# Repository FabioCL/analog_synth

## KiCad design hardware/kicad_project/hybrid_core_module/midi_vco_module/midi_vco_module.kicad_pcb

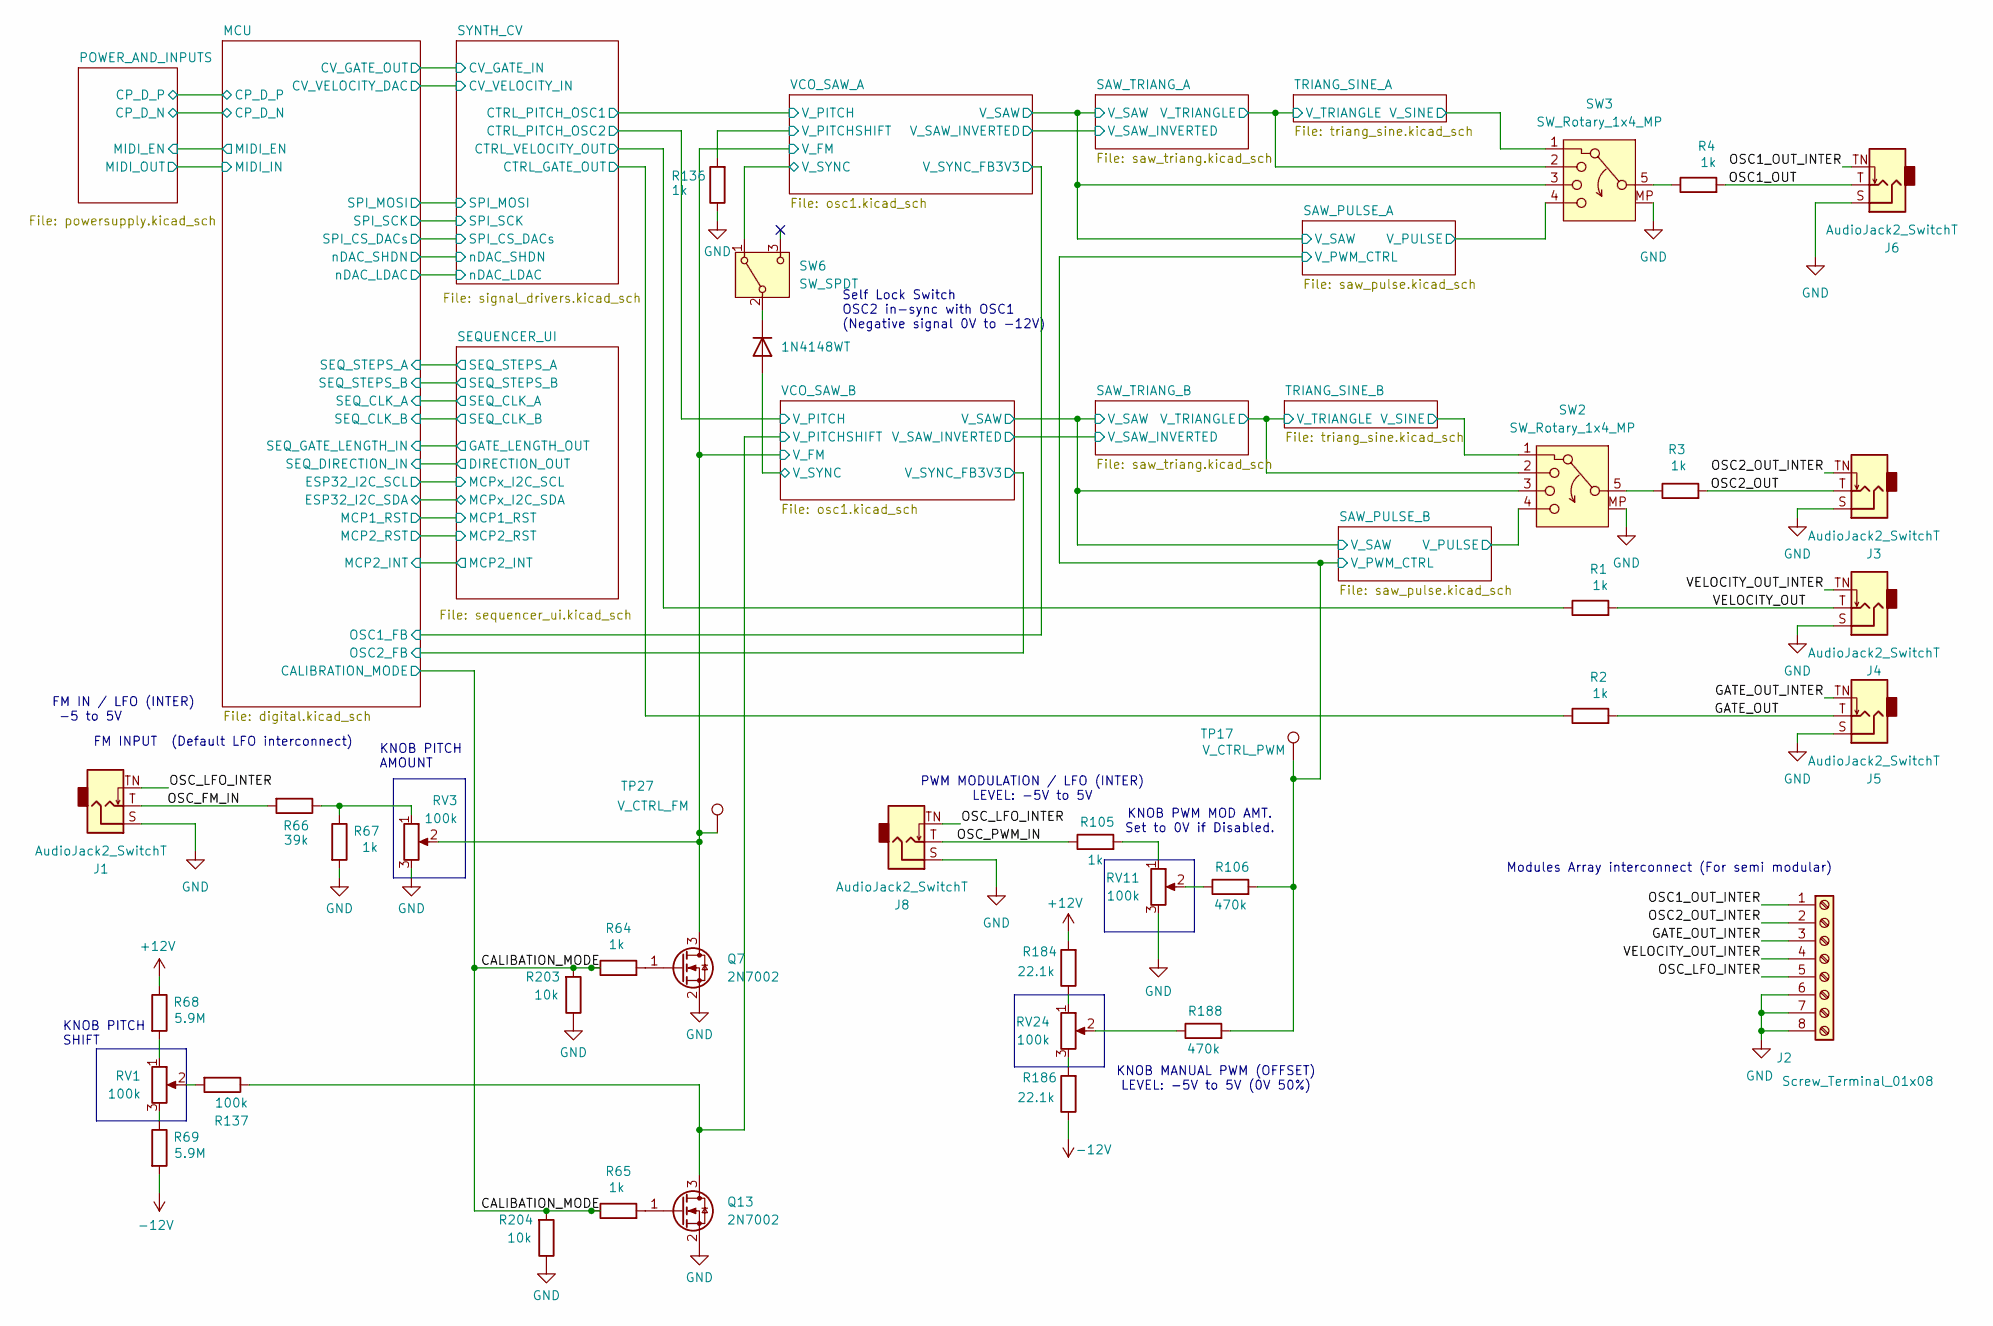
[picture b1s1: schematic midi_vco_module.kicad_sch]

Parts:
D1: 1N4148WT; D_SOD-523; Manufacturer PartNumer 1N4148WT
J1, J3, J4, J5, J6, J8: AudioJack2_SwitchT; Jack_3.5mm_QingPu_WQP-PJ398SM_Vertical_CircularHoles; Manufacturer PartNumer WQP-PJ398SM
J2: Screw_Terminal_01x08; TerminalBlock_CUI_TB007-508-08_1x08_P5.08mm_Horizontal; Manufacturer PartNumer TB007-508-08BE
Q7, Q13: 2N7002; SOT-23; Manufacturer PartNumer 2N7002
R1, R2, R3, R4, R64, R65, R67, R105, R136: 1k; R_0402_1005Metric; Manufacturer PartNumer RT0402FRE071KL
R66: 39k; R_0402_1005Metric; Manufacturer PartNumer RT0402FRE0739KL
R68, R69: 5.9M; R_0402_1005Metric; Manufacturer PartNumer RC0402FR-075M9L
R106, R188: 470k; R_0402_1005Metric; Manufacturer PartNumer RC0402FR-7D470KL
R137: 100k; R_0402_1005Metric; Manufacturer PartNumer RT0402FRE07100KL
R184, R186: 22.1k; R_0402_1005Metric; Manufacturer PartNumer RT0402FRE0721KL
R203, R204: 10k; R_0402_1005Metric; Manufacturer PartNumer RT0402FRE0710KL
RV1, RV3, RV11, RV24: 100k; Potentiometer_RV09_Single_Vertical; Manufacturer PartNumer 3296W-104-LF
SW2, SW3: SW_Rotary_1x4_MP; SR16 Rotary Band Switch; Manufacturer PartNumer SR16
SW6: SW_SPDT; SW_Toggle_Blue_wSlots; Manufacturer PartNumer MTS-102
TP17: V_CTRL_PWM; TestPoint_Pad_1.0x1.0mm
TP27: V_CTRL_FM; TestPoint_Pad_1.0x1.0mm

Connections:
+12V: R68.1, R184.2; also elsewhere on the board
-12V: R69.2, R186.1; also elsewhere on the board
/CALIBATION_MODE: R64.1, R65.1, R203.2, R204.2; also elsewhere on the board
/GATE_OUT: J5.T, R2.2
/GATE_OUT_INTER: J2.3, J5.TN
/OSC1_OUT: J6.T, R4.2
/OSC1_OUT_INTER: J2.1, J6.TN
/OSC2_OUT: J3.T, R3.2
/OSC2_OUT_INTER: J2.2, J3.TN
/OSC_FM_IN: J1.T, R66.2
/OSC_LFO_INTER: J1.TN, J2.5, J8.TN
/OSC_PWM_IN: J8.T, R105.1
/SAW_PULSE_A/V_PULSE: SW3.4; also elsewhere on the board
/SAW_PULSE_A/V_PWM_CTRL: R106.2, R188.2, TP17.1; also elsewhere on the board
/SAW_PULSE_A/V_SAW: SW3.3; also elsewhere on the board
/SAW_PULSE_B/V_PULSE: SW2.4; also elsewhere on the board
/SAW_PULSE_B/V_SAW: SW2.3; also elsewhere on the board
/SAW_TRIANG_A/V_TRIANGLE: SW3.2; also elsewhere on the board
/SAW_TRIANG_B/V_TRIANGLE: SW2.2; also elsewhere on the board
/SYNTH_CV/CTRL_GATE_OUT: R2.1; also elsewhere on the board
/SYNTH_CV/CTRL_VELOCITY_OUT: R1.1; also elsewhere on the board
/TRIANG_SINE_A/V_SINE: SW3.1; also elsewhere on the board
/TRIANG_SINE_B/V_SINE: SW2.1; also elsewhere on the board
/VCO_SAW_A/V_FM: Q7.3 (D), RV3.2, TP27.1; also elsewhere on the board
/VCO_SAW_A/V_PITCHSHIFT: R136.2; also elsewhere on the board
/VCO_SAW_A/V_SYNC: SW6.1 (A); also elsewhere on the board
/VCO_SAW_B/V_PITCHSHIFT: Q13.3 (D), R137.1; also elsewhere on the board
/VCO_SAW_B/V_SYNC: D1.2 (A); also elsewhere on the board
/VELOCITY_OUT: J4.T, R1.2
/VELOCITY_OUT_INTER: J2.4, J4.TN
GND: J1.S, J2.6, J2.7, J2.8, J3.S, J4.S, J5.S, J6.S, J8.S, Q7.2 (S), Q13.2 (S), R67.2, R136.1, R203.1, R204.1, RV3.3, RV11.3, SW2.MP, SW3.MP; also elsewhere on the board
unnamed: D1.1 (K), SW6.2 (B)
unnamed: Q7.1 (G), R64.2
unnamed: Q13.1 (G), R65.2
unnamed: R3.1, SW2.5
unnamed: R4.1, SW3.5
unnamed: R66.1, R67.1, RV3.1
unnamed: R68.2, RV1.1
unnamed: R69.1, RV1.3
unnamed: R105.2, RV11.1
unnamed: R106.1, RV11.2
unnamed: R137.2, RV1.2
unnamed: R184.1, RV24.1
unnamed: R186.2, RV24.3
unnamed: R188.1, RV24.2

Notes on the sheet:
KNOB PITCH SHIFT
KNOB PWM MOD AMT. Set to 0V if Disabled.
Self Lock Switch OSC2 in-sync with OSC1 (Negative signal 0V to -12V)
PWM MODULATION / LFO (INTER) LEVEL: -5V to 5V
FM INPUT (Default LFO interconnect)
KNOB MANUAL PWM (OFFSET) LEVEL: -5V to 5V (0V 50%)
KNOB PITCH AMOUNT
FM IN / LFO (INTER) -5 to 5V
Modules Array interconnect (For semi modular)

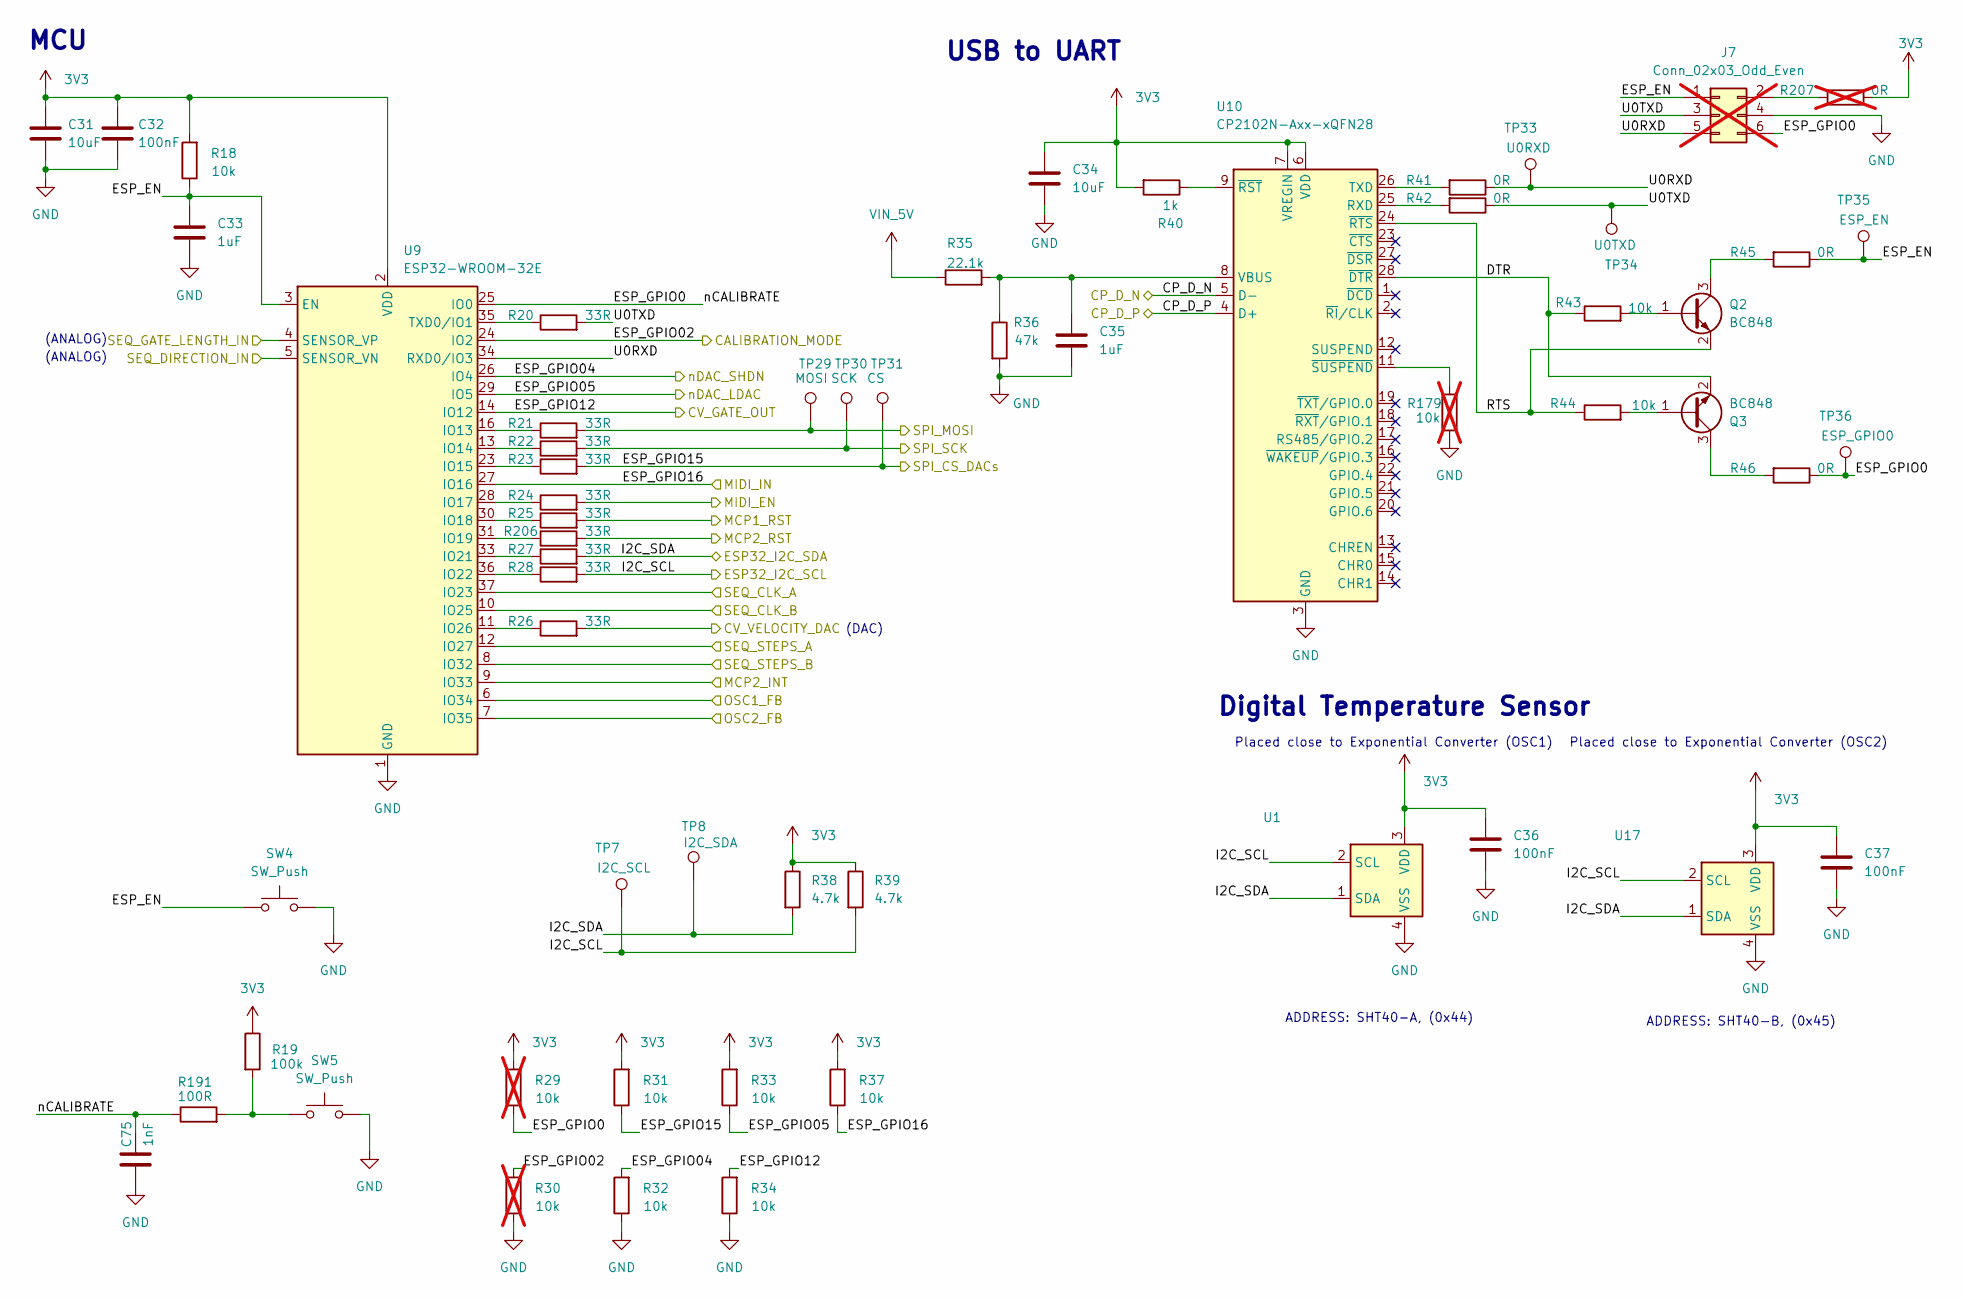
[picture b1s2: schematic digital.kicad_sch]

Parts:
C31, C34: 10uF; C_0805_2012Metric; Manufacturer PartNumer GRM21BR61E106KA73K
C32, C36, C37: 100nF; C_0402_1005Metric; Manufacturer PartNumer GRM155R71E104KE14J
C33, C35: 1uF; C_0805_2012Metric; Manufacturer PartNumer GRM219R71E105MA88J
C75: 1nF; C_0402_1005Metric; Manufacturer PartNumer GRM155R71E103KA01J
J7: Conn_02x03_Odd_Even; PinHeader_2x03_P1.27mm_Vertical_SMD; not fitted
Q2, Q3: BC848; SOT-23; Manufacturer PartNumer BC848A
R18, R31, R32, R33, R34, R37, R43, R44: 10k; R_0402_1005Metric; Manufacturer PartNumer RT0402FRE0710KL
R19: 100k; R_0402_1005Metric; Manufacturer PartNumer RT0402FRE07100KL
R20, R21, R22, R23, R24, R25, R26, R27, R28, R206: 33R; R_0402_1005Metric; Manufacturer PartNumer RT0402FRE0733RL
R29, R30, R179: 10k; R_0402_1005Metric; Manufacturer PartNumer RT0402FRE0710KL; not fitted
R35: 22.1k; R_0402_1005Metric; Manufacturer PartNumer RT0402FRE0721KL
R36: 47k; R_0402_1005Metric; Manufacturer PartNumer RT0402FRE0747KL
R38, R39: 4.7k; R_0402_1005Metric; Manufacturer PartNumer RT0402FRE074K7L
R40: 1k; R_0402_1005Metric; Manufacturer PartNumer RT0402FRE071KL
R41, R42, R45, R46: 0R; R_0402_1005Metric; Manufacturer PartNumer RC0402FR-070RL
R191: 100R; R_0402_1005Metric; Manufacturer PartNumer RT0402FRE07100RL
R207: 0R; R_0402_1005Metric; Manufacturer PartNumer RC0402FR-070RL; not fitted
SW4, SW5: SW_Push; SW_PUSH_6mm
TP7: I2C_SCL; TestPoint_Pad_1.0x1.0mm
TP8: I2C_SDA; TestPoint_Pad_1.0x1.0mm
TP29: MOSI; TestPoint_Pad_1.0x1.0mm
TP30: SCK; TestPoint_Pad_1.0x1.0mm
TP31: CS; TestPoint_Pad_1.0x1.0mm
TP33: U0RXD; TestPoint_Pad_1.0x1.0mm
TP34: U0TXD; TestPoint_Pad_1.0x1.0mm
TP35: ESP_EN; TestPoint_Pad_1.0x1.0mm
TP36: ESP_GPIO0; TestPoint_Pad_1.0x1.0mm
U1: SHT4x; Sensirion_DFN-4_1.5x1.5mm_P0.8mm_SHT4x_NoCentralPad; Manufacturer PartNumer SHT40-AD1B-R3
U9: ESP32-WROOM-32E; ESP32-WROOM-32D; Manufacturer PartNumer ESP32-WROOM-32E-N8
U10: CP2102N-Axx-xQFN28; QFN-28-1EP_5x5mm_P0.5mm_EP3.35x3.35mm; Manufacturer PartNumer CP2102N-A02-GQFN28R
U17: SHT4x; Sensirion_DFN-4_1.5x1.5mm_P0.8mm_SHT4x_NoCentralPad; Manufacturer PartNumer SHT40-BD1B-R3

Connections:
3V3: C31.1, C32.1, C34.1, C36.1, C37.1, R18.2, R19.1, R29.2, R31.2, R33.2, R37.2, R38.1, R39.1, R40.2, R207.1, U1.3 (VDD), U9.2 (VDD), U10.6 (VDD), U10.7 (VREGIN), U17.3 (VDD); also elsewhere on the board
/CALIBATION_MODE: R30.2, U9.24 (IO2); also elsewhere on the board
/MCU/CP_D_N: U10.5 (D-); also elsewhere on the board
/MCU/CP_D_P: U10.4 (D+); also elsewhere on the board
/MCU/CV_VELOCITY_DAC: R26.2; also elsewhere on the board
/MCU/DTR: Q3.2 (E), R43.1, U10.28 (~DTR)
/MCU/ESP_EN: C33.1, J7.1, R18.1, R45.1, SW4.1, TP35.1, U9.3 (EN)
/MCU/ESP_GPIO0: C75.2, J7.6, R29.1, R46.1, R191.1, TP36.1, U9.25 (IO0)
/MCU/ESP_GPIO04: R32.2, U9.26 (IO4); also elsewhere on the board
/MCU/ESP_GPIO05: R33.1, U9.29 (IO5); also elsewhere on the board
/MCU/ESP_GPIO12: R34.2, U9.14 (IO12); also elsewhere on the board
/MCU/ESP_GPIO15: R23.2, R31.1, TP31.1; also elsewhere on the board
/MCU/ESP_GPIO16: R37.1, U9.27 (IO16); also elsewhere on the board
/MCU/I2C_SCL: R28.2, R39.2, TP7.1, U1.2 (SCL), U17.2 (SCL); also elsewhere on the board
/MCU/I2C_SDA: R27.2, R38.2, TP8.1, U1.1 (SDA), U17.1 (SDA); also elsewhere on the board
/MCU/MCP2_INT: U9.9 (IO33); also elsewhere on the board
/MCU/MCP2_RST: R206.2; also elsewhere on the board
/MCU/MIDI_EN: R24.2; also elsewhere on the board
/MCU/OSC1_FB: U9.6 (IO34); also elsewhere on the board
/MCU/OSC2_FB: U9.7 (IO35); also elsewhere on the board
/MCU/RTS: Q2.2 (E), R44.1, U10.24 (~RTS)
/MCU/SEQ_CLK_A: U9.37 (IO23); also elsewhere on the board
/MCU/SEQ_CLK_B: U9.10 (IO25); also elsewhere on the board
/MCU/SEQ_DIRECTION_IN: U9.5 (SENSOR_VN); also elsewhere on the board
/MCU/SEQ_GATE_LENGTH_IN: U9.4 (SENSOR_VP); also elsewhere on the board
/MCU/SEQ_STEPS_A: U9.12 (IO27); also elsewhere on the board
/MCU/SEQ_STEPS_B: U9.8 (IO32); also elsewhere on the board
/MCU/U0RXD: J7.5, R41.1, TP33.1, U9.34 (RXD0/IO3)
/MCU/U0TXD: J7.3, R20.2, R42.1, TP34.1
/SEQUENCER_UI/MCP_RST: R25.2; also elsewhere on the board
/SYNTH_CV/SPI_MOSI: R21.2, TP29.1; also elsewhere on the board
/SYNTH_CV/SPI_SCK: R22.2, TP30.1; also elsewhere on the board
GND: C31.2, C32.2, C33.2, C34.2, C35.2, C36.2, C37.2, C75.1, J7.4, R30.1, R32.1, R34.1, R36.2, R179.1, SW4.2, SW5.2, U1.4 (VSS), U9.1 (GND), U9.15 (GND), U9.38 (GND), U9.39 (GND), U10.3 (GND), U10.29 (GND), U17.4 (VSS); also elsewhere on the board
unnamed: J7.2, R207.2
unnamed: Q2.1 (B), R43.2
unnamed: Q2.3 (C), R45.2
unnamed: Q3.1 (B), R44.2
unnamed: Q3.3 (C), R46.2
unnamed: R19.2, R191.2, SW5.1
unnamed: R21.1, U9.16 (IO13)
unnamed: R22.1, U9.13 (IO14)
unnamed: R23.1, U9.23 (IO15)
unnamed: R24.1, U9.28 (IO17)
unnamed: R25.1, U9.30 (IO18)
unnamed: R206.1, U9.31 (IO19)
unnamed: R27.1, U9.33 (IO21)
unnamed: R28.1, U9.36 (IO22)
unnamed: R26.1, U9.11 (IO26)
unnamed: R20.1, U9.35 (TXD0/IO1)
unnamed: R42.2, U10.25 (RXD)
unnamed: R41.2, U10.26 (TXD)
unnamed: C35.1, R35.2, R36.1, U10.8 (VBUS)
unnamed: R40.1, U10.9 (~RST)
unnamed: R179.2, U10.11 (~SUSPEND)
VIN_5V: R35.1; also elsewhere on the board

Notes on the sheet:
ADDRESS: SHT40-A, (0x44)
USB to UART
Placed close to Exponential Converter (OSC1)
Placed close to Exponential Converter (OSC2)
(ANALOG)
(DAC)
ADDRESS: SHT40-B, (0x45)
Digital Temperature Sensor
MCU

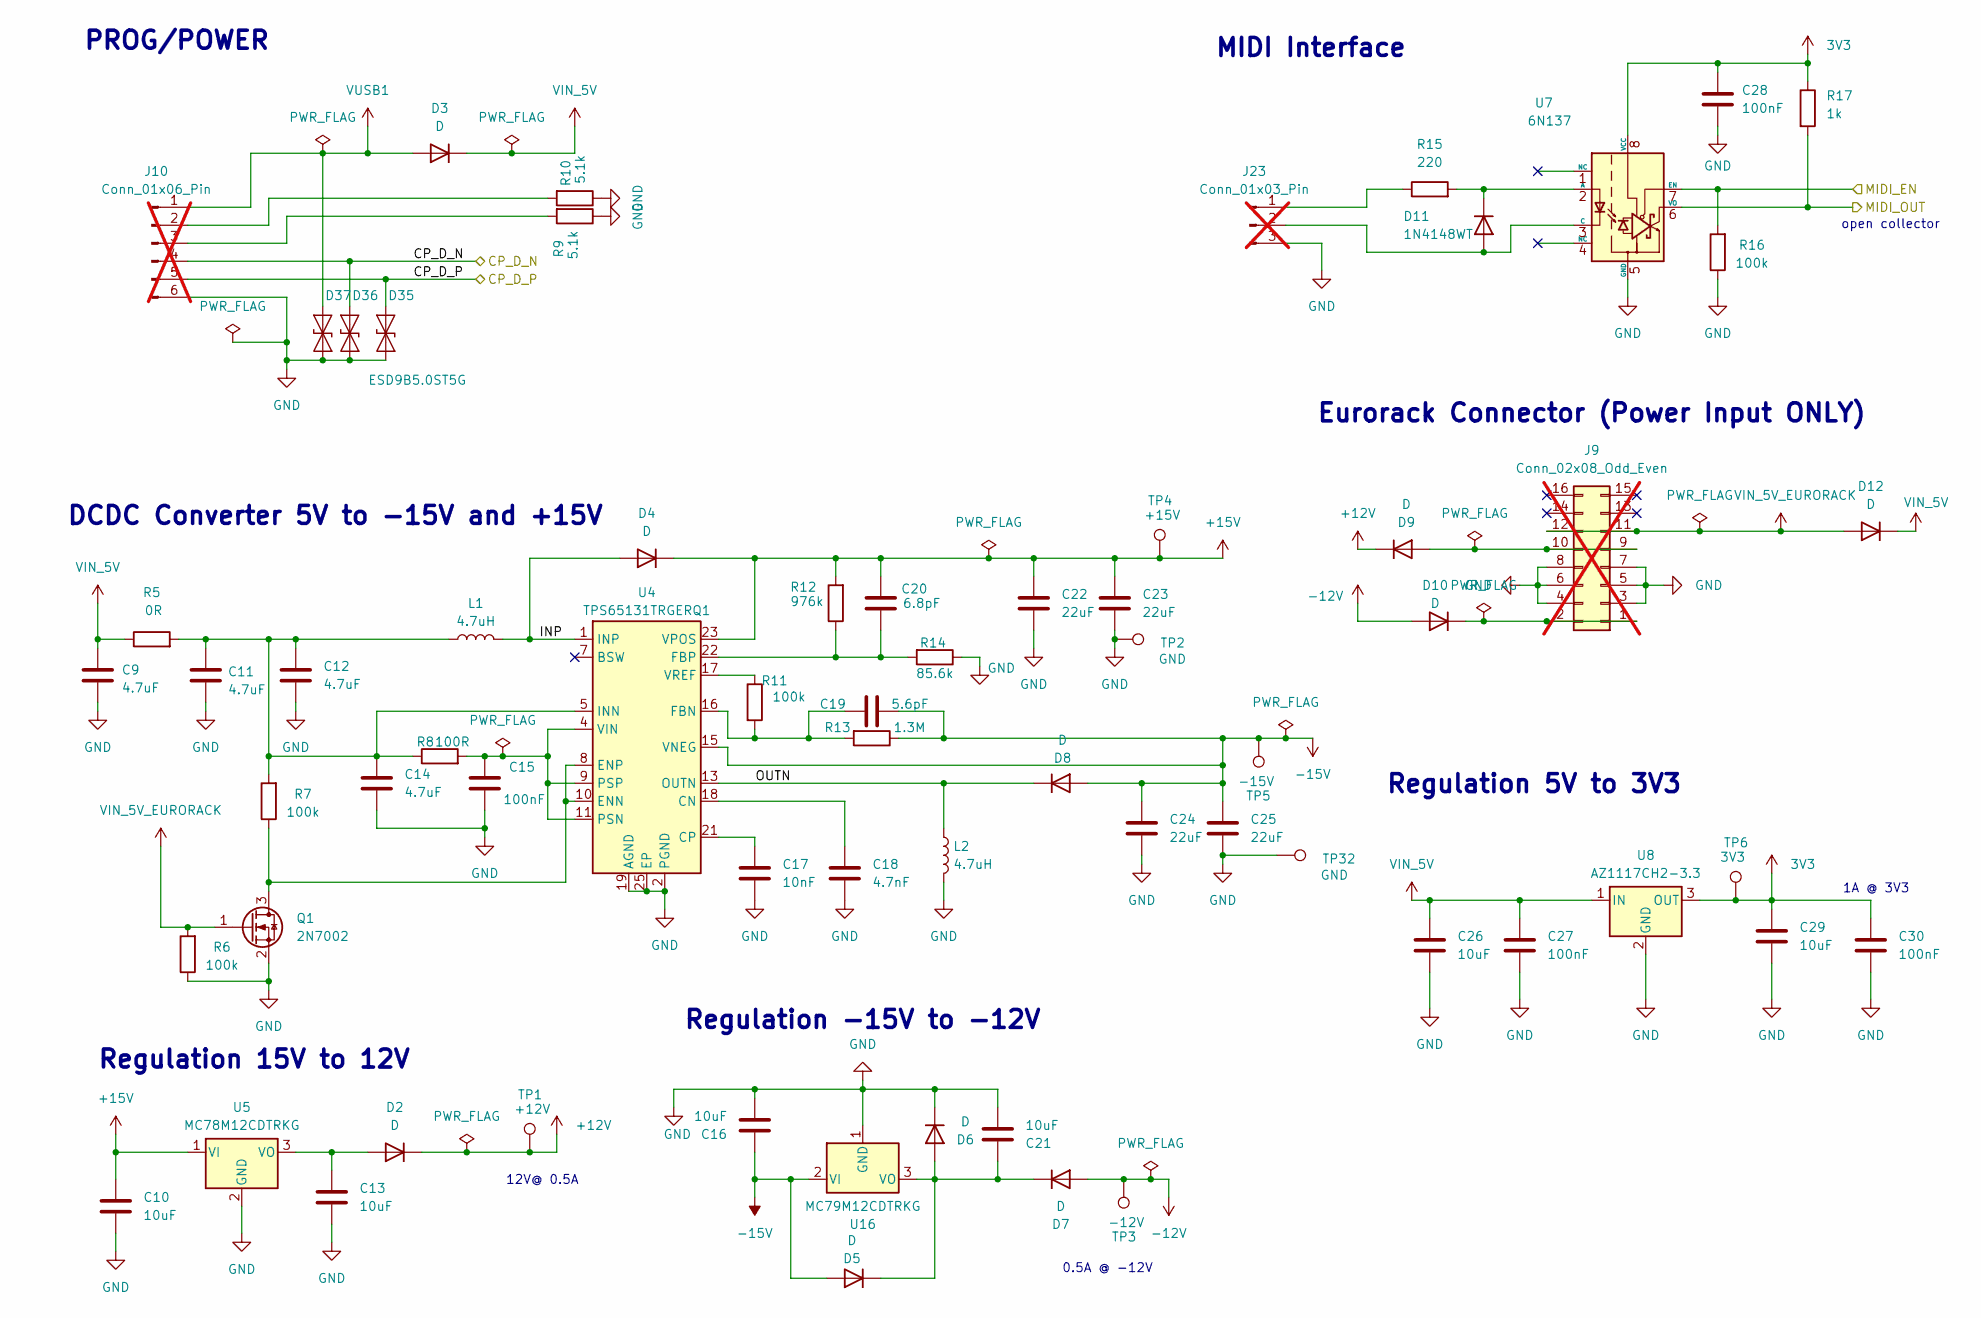
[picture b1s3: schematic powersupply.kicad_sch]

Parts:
C9, C11, C12, C14: 4.7uF; C_0805_2012Metric; Manufacturer PartNumer GRM219R61E475MA73D
C10, C13, C16, C21, C26, C29: 10uF; C_0805_2012Metric; Manufacturer PartNumer GRM21BR61E106KA73K
C15, C27, C28, C30: 100nF; C_0402_1005Metric; Manufacturer PartNumer GRM155R71E104KE14J
C17: 10nF; C_0402_1005Metric; Manufacturer PartNumer GRM155R71E103KA01D
C18: 4.7nF; C_0402_1005Metric; Manufacturer PartNumer GRM155R71E472KA01J
C19: 5.6pF; C_0402_1005Metric; Manufacturer PartNumer GJM1555C1H5R6BB01J
C20: 6.8pF; C_0402_1005Metric; Manufacturer PartNumer GJM1555C1H6R8DB01D
C22, C23, C24, C25: 22uF; C_1210_3225Metric; Manufacturer PartNumer CL32A226KAJNNNE
D2, D3, D4, D5, D6, D7, D8, D9, D10, D12: D; D_Powermite_AK; Manufacturer PartNumer MBRM120LT1G
D11: 1N4148WT; D_SOD-523; Manufacturer PartNumer 1N4148WT
D35, D36, D37: ESD9B5.0ST5G; D_SOD-923; Manufacturer PartNumer ESD9B5.0ST5G
J9: Conn_02x08_Odd_Even; PinHeader_2x08_P2.54mm_Vertical; Manufacturer PartNumer TST-108-02-T-D; not fitted
J10: Conn_01x06_Pin; PinHeader_1x06_P2.54mm_Vertical; not fitted
J23: Conn_01x03_Pin; PinHeader_1x03_P2.54mm_Vertical; not fitted
L1, L2: 4.7uH; L_TDK_SLF6028; Manufacturer PartNumer SLF6028T-4R7M1R6-PF
Q1: 2N7002; SOT-23; Manufacturer PartNumer 2N7002
R5: 0R; R_1210_3225Metric; Manufacturer PartNumer RC0402FR-070RL
R6, R7, R11, R16: 100k; R_0402_1005Metric; Manufacturer PartNumer RT0402FRE07100KL
R8: 100R; R_0402_1005Metric; Manufacturer PartNumer RT0402FRE07100RL
R9, R10: 5.1k; R_0402_1005Metric; Manufacturer PartNumer RT0402FRE075K1L
R12: 976k; R_0402_1005Metric; Manufacturer PartNumer RC0402FR-07976KL
R13: 1.3M; R_0402_1005Metric; Manufacturer PartNumer RC0402FR-071M3L
R14: 85.6k; R_0402_1005Metric; Manufacturer PartNumer RT0402BRE0785K6L
R15: 220; R_0402_1005Metric; Manufacturer PartNumer RT0402FRE07220RL
R17: 1k; R_0402_1005Metric; Manufacturer PartNumer RT0402FRE071KL
TP1: +12V; TestPoint_Pad_1.0x1.0mm
TP2, TP32: GND; TestPoint_Pad_1.0x1.0mm
TP3: -12V; TestPoint_Pad_1.0x1.0mm
TP4: +15V; TestPoint_Pad_1.0x1.0mm
TP5: -15V; TestPoint_Pad_1.0x1.0mm
TP6: 3V3; TestPoint_Pad_1.0x1.0mm
U4: TPS65131TRGERQ1; VQFN-24-1EP_4x4mm_P0.5mm_EP2.45x2.45mm_ThermalVias; Manufacturer PartNumer TPS65131TRGERQ1
U5: MC78M12CDTRKG; TO-252-2; Manufacturer PartNumer MC78M12CDTRKG
U7: 6N137; DIP-8_W7.62mm; Manufacturer PartNumer 6N137-X007T
U8: AZ1117CH2-3.3; SOT-223-3_TabPin2; Manufacturer PartNumer AZ1117CH2-3.3TRG1
U16: MC79M12CDTRKG; TO-252-2; Manufacturer PartNumer MC79M12CDTRKG

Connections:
3V3: C28.1, C29.1, C30.1, R17.1, TP6.1, U7.8 (VCC), U8.3 (OUT); also elsewhere on the board
+12V: D2.1 (K), D9.1 (K), TP1.1; also elsewhere on the board
+15V: C10.1, C20.1, C22.1, C23.1, D4.1 (K), R12.2, TP4.1, U4.23 (VPOS), U5.1 (VI)
-12V: D7.2 (A), D10.2 (A), TP3.1; also elsewhere on the board
-15V: C16.1, C19.2, C24.1, C25.1, D5.2 (A), D8.2 (A), R13.1, TP5.1, U4.15 (VNEG), U16.2 (VI)
/MCU/CP_D_N: D36.2 (A2), J10.4; also elsewhere on the board
/MCU/CP_D_P: D35.2 (A2), J10.5; also elsewhere on the board
/MCU/ESP_GPIO16: R17.2, U7.6 (VO); also elsewhere on the board
/MCU/MIDI_EN: R16.2, U7.7 (EN); also elsewhere on the board
/POWER_AND_INPUTS/INP: D4.2 (A), L1.2, U4.1 (INP), U4.24 (INP)
/POWER_AND_INPUTS/OUTN: D8.1 (K), L2.1, U4.13 (OUTN), U4.14 (OUTN)
GND: C9.2, C10.2, C11.2, C12.2, C13.2, C14.2, C15.2, C16.2, C17.2, C18.2, C21.2, C22.2, C23.2, C24.2, C25.2, C26.2, C27.2, C28.2, C29.2, C30.2, D6.1 (K), D35.1 (A1), D36.1 (A1), D37.1 (A1), J9.3, J9.4, J9.5, J9.6, J9.7, J9.8, J10.6, J23.3, L2.2, Q1.2 (S), R6.1, R9.1, R10.1, R14.1, R16.1, TP2.1, TP32.1, U4.2 (PGND), U4.3 (PGND), U4.19 (AGND), U4.25 (EP), U5.2 (GND), U7.5 (GND), U8.2 (GND), U16.1 (GND); also elsewhere on the board
unnamed: C11.1, C12.1, C14.1, L1.1, R5.2, R7.2, R8.1, U4.5 (INN), U4.6 (INN)
unnamed: C13.1, D2.2 (A), U5.3 (VO)
unnamed: C21.1, D5.1 (K), D6.2 (A), D7.1 (K), U16.3 (VO)
unnamed: D9.2 (A), J9.9, J9.10
unnamed: D10.1 (K), J9.1, J9.2
unnamed: D11.2 (A), J23.2, U7.3 (C)
unnamed: D11.1 (K), R15.2, U7.2 (A)
unnamed: J10.2, R10.2
unnamed: J10.3, R9.2
unnamed: J23.1, R15.1
unnamed: Q1.3 (D), R7.1, U4.8 (ENP), U4.10 (ENN)
unnamed: C18.1, U4.18 (CN)
unnamed: C17.1, U4.21 (CP)
unnamed: C19.1, R11.2, R13.2, U4.16 (FBN)
unnamed: C20.2, R12.1, R14.2, U4.22 (FBP)
unnamed: C15.1, R8.2, U4.4 (VIN), U4.9 (PSP), U4.11 (PSN)
unnamed: R11.1, U4.17 (VREF)
VIN_5V: C9.1, C26.1, C27.1, D3.1 (K), D12.1 (K), R5.1, U8.1 (IN); also elsewhere on the board
VIN_5V_EURORACK: D12.2 (A), J9.11, J9.12, Q1.1 (G), R6.2
VUSB1: D3.2 (A), D37.2 (A2), J10.1

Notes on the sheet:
12V@ 0.5A
DCDC Converter 5V to -15V and +15V
0.5A @ -12V
Regulation -15V to -12V
MIDI Interface
Regulation 15V to 12V
1A @ 3V3
Eurorack Connector (Power Input ONLY)
Regulation 5V to 3V3
open collector
PROG/POWER

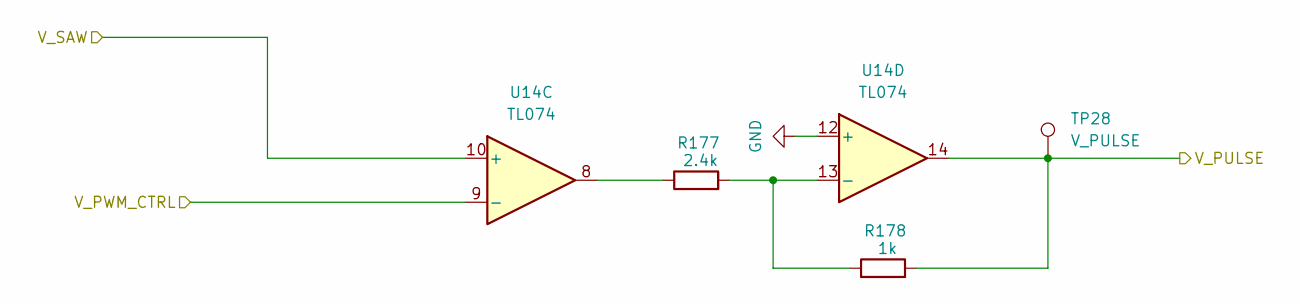
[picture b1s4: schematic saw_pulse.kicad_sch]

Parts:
R177: 2.4k; R_0402_1005Metric; Manufacturer PartNumer RT0402BRD072K4L
R178: 1k; R_0402_1005Metric; Manufacturer PartNumer RT0402FRE071KL
TP28: V_PULSE; TestPoint_Pad_1.0x1.0mm
U14: TL074; SOIC-14_3.9x8.7mm_P1.27mm; Manufacturer PartNumer TL074HIDR

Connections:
/SAW_PULSE_A/V_PULSE: R178.2, TP28.1, U14.14; also elsewhere on the board
/SAW_PULSE_A/V_PWM_CTRL: U14.9 (-); also elsewhere on the board
/SAW_PULSE_A/V_SAW: U14.10 (+); also elsewhere on the board
GND: U14.12 (+); also elsewhere on the board
unnamed: R177.1, U14.8
unnamed: R177.2, R178.1, U14.13 (-)

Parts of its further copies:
R107: 2.4k; R_0402_1005Metric; Manufacturer PartNumer RT0402BRD072K4L
R108: 1k; R_0402_1005Metric; Manufacturer PartNumer RT0402FRE071KL
TP18: V_PULSE; TestPoint_Pad_1.0x1.0mm
U24: TL074; SOIC-14_3.9x8.7mm_P1.27mm; Manufacturer PartNumer TL074HIDR

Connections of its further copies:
+12V: U24.4 (V+); also elsewhere on the board
-12V: U24.11 (V-); also elsewhere on the board
/SAW_PULSE_A/V_PWM_CTRL: U24.9 (-); also elsewhere on the board
/SAW_PULSE_B/V_PULSE: R108.2, TP18.1, U24.14; also elsewhere on the board
/SAW_PULSE_B/V_SAW: U24.10 (+); also elsewhere on the board
/SAW_TRIANG_B/V_TRIANGLE: U24.1; also elsewhere on the board
/TRIANG_SINE_B/V_SINE: U24.7; also elsewhere on the board
GND: U24.12 (+); also elsewhere on the board
unnamed 158: U24.5 (+); also elsewhere on the board
unnamed: R107.1, U24.8
unnamed 268: U24.3 (+); also elsewhere on the board
unnamed 269: U24.2 (-); also elsewhere on the board
unnamed 270: U24.6 (-); also elsewhere on the board
unnamed: R107.2, R108.1, U24.13 (-)

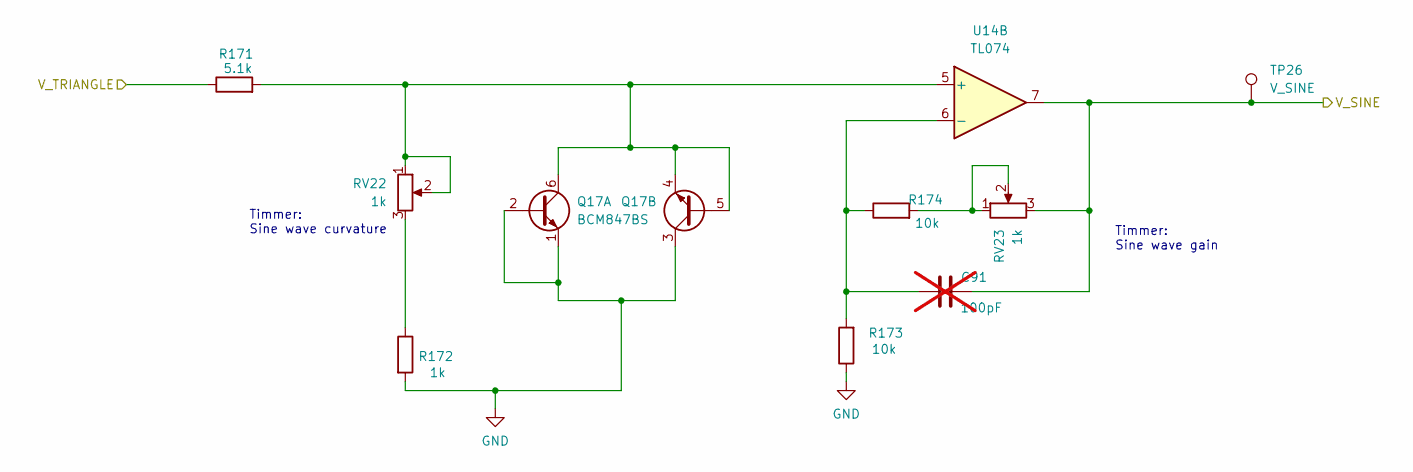
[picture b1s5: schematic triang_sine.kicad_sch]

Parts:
C91: 100pF; C_0402_1005Metric; Manufacturer PartNumer GCM1555C1H101FA16J; not fitted
Q17: BCM847BS; SOT-363_SC-70-6; Manufacturer PartNumer BCM847BS
R171: 5.1k; R_0402_1005Metric; Manufacturer PartNumer RT0402FRE075K1L
R172: 1k; R_0402_1005Metric; Manufacturer PartNumer RT0402FRE071KL
R173, R174: 10k; R_0402_1005Metric; Manufacturer PartNumer RT0402FRE0710KL
RV22, RV23: 1k; Potentiometer_Bourns_3296W_Vertical; Manufacturer PartNumer 3296W-102-LF
TP26: V_SINE; TestPoint_Pad_1.0x1.0mm
U14: TL074; SOIC-14_3.9x8.7mm_P1.27mm; Manufacturer PartNumer TL074HIDR

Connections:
/SAW_TRIANG_A/V_TRIANGLE: R171.1; also elsewhere on the board
/TRIANG_SINE_A/V_SINE: C91.2, RV23.3, TP26.1, U14.7; also elsewhere on the board
GND: Q17.1 (E1), Q17.2 (B1), Q17.3 (C2), R172.2, R173.1; also elsewhere on the board
unnamed: Q17.4 (E2), Q17.5 (B2), Q17.6 (C1), R171.2, RV22.1, RV22.2, U14.5 (+)
unnamed: R172.1, RV22.3
unnamed: R174.2, RV23.1, RV23.2
unnamed: C91.1, R173.2, R174.1, U14.6 (-)

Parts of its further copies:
C66: 100pF; C_0402_1005Metric; Manufacturer PartNumer GCM1555C1H101FA16J; not fitted
Q11: BCM847BS; SOT-363_SC-70-6; Manufacturer PartNumer BCM847BS
R101: 5.1k; R_0402_1005Metric; Manufacturer PartNumer RT0402FRE075K1L
R102: 1k; R_0402_1005Metric; Manufacturer PartNumer RT0402FRE071KL
R103, R104: 10k; R_0402_1005Metric; Manufacturer PartNumer RT0402FRE0710KL
RV9, RV10: 1k; Potentiometer_Bourns_3296W_Vertical; Manufacturer PartNumer 3296W-102-LF
TP16: V_SINE; TestPoint_Pad_1.0x1.0mm
U24: TL074; SOIC-14_3.9x8.7mm_P1.27mm; Manufacturer PartNumer TL074HIDR

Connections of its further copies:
+12V: U24.4 (V+); also elsewhere on the board
-12V: U24.11 (V-); also elsewhere on the board
/SAW_PULSE_A/V_PWM_CTRL: U24.9 (-); also elsewhere on the board
/SAW_PULSE_B/V_PULSE: U24.14; also elsewhere on the board
/SAW_PULSE_B/V_SAW: U24.10 (+); also elsewhere on the board
/SAW_TRIANG_B/V_TRIANGLE: R101.1, U24.1; also elsewhere on the board
/TRIANG_SINE_B/V_SINE: C66.2, RV10.3, TP16.1, U24.7; also elsewhere on the board
GND: Q11.1 (E1), Q11.2 (B1), Q11.3 (C2), R102.2, R103.1, U24.12 (+); also elsewhere on the board
unnamed: Q11.4 (E2), Q11.5 (B2), Q11.6 (C1), R101.2, RV9.1, RV9.2, U24.5 (+)
unnamed: R102.1, RV9.3
unnamed: R104.2, RV10.1, RV10.2
unnamed 190: U24.8; also elsewhere on the board
unnamed 268: U24.3 (+); also elsewhere on the board
unnamed 269: U24.2 (-); also elsewhere on the board
unnamed: C66.1, R103.2, R104.1, U24.6 (-)
unnamed 271: U24.13 (-); also elsewhere on the board

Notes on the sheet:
Timmer: Sine wave gain
Timmer: Sine wave curvature

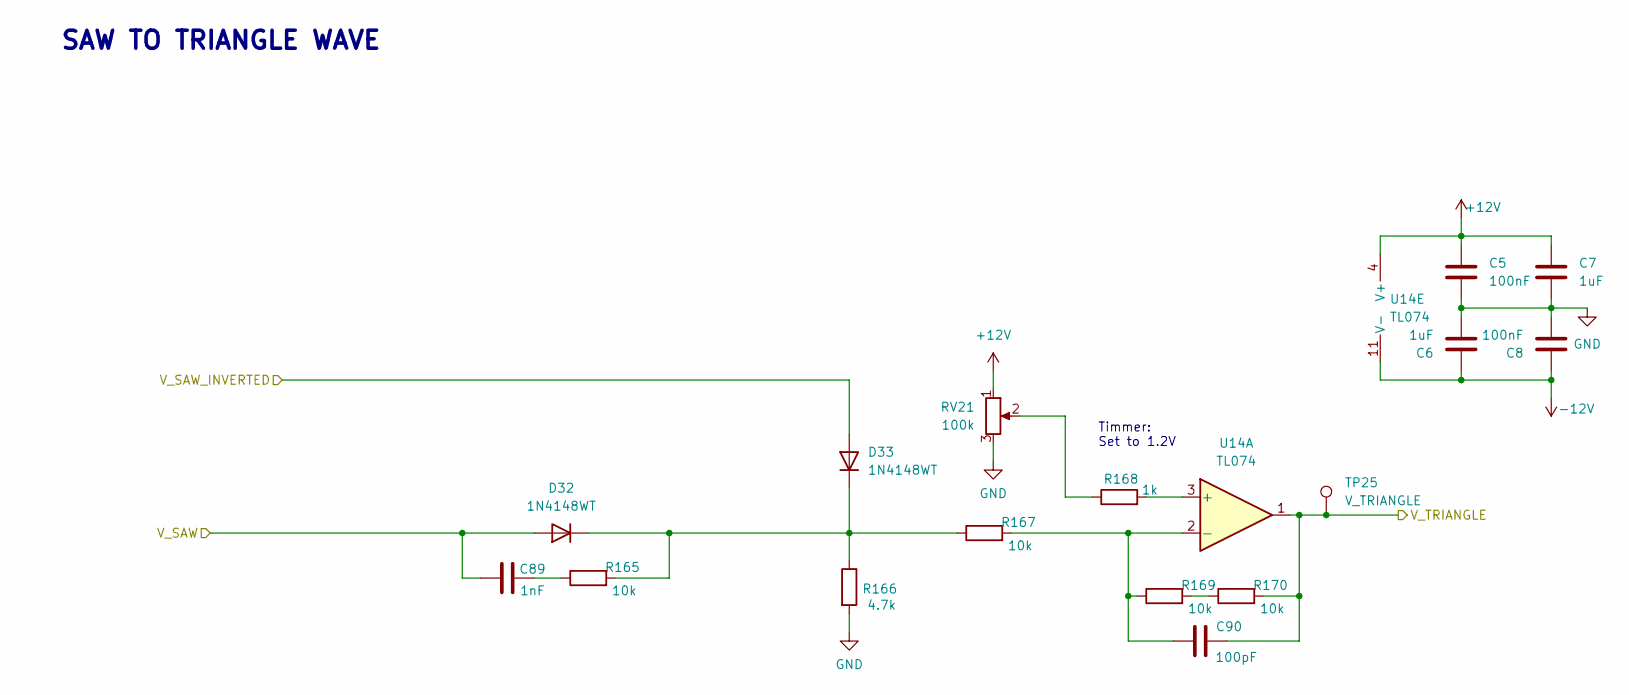
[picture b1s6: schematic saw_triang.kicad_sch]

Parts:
C5, C8: 100nF; C_0402_1005Metric; Manufacturer PartNumer GRM155R71E104KE14J
C6, C7: 1uF; C_0805_2012Metric; Manufacturer PartNumer GRM219R71E105MA88J
C89: 1nF; C_0402_1005Metric; Manufacturer PartNumer GRM155R71E103KA01J
C90: 100pF; C_0402_1005Metric; Manufacturer PartNumer GCM1555C1H101FA16J
D32, D33: 1N4148WT; D_SOD-523; Manufacturer PartNumer 1N4148WT
R165, R167, R169, R170: 10k; R_0402_1005Metric; Manufacturer PartNumer RT0402FRE0710KL
R166: 4.7k; R_0402_1005Metric; Manufacturer PartNumer RT0402FRE074K7L
R168: 1k; R_0402_1005Metric; Manufacturer PartNumer RT0402FRE071KL
RV21: 100k; Potentiometer_Bourns_3296W_Vertical; Manufacturer PartNumer 3296W-104-LF
TP25: V_TRIANGLE; TestPoint_Pad_1.0x1.0mm
U14: TL074; SOIC-14_3.9x8.7mm_P1.27mm; Manufacturer PartNumer TL074HIDR

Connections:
+12V: C5.1, C7.1, RV21.1, U14.4 (V+); also elsewhere on the board
-12V: C6.1, C8.1, U14.11 (V-); also elsewhere on the board
/SAW_PULSE_A/V_SAW: C89.1, D32.2 (A); also elsewhere on the board
/SAW_TRIANG_A/V_SAW_INVERTED: D33.2 (A); also elsewhere on the board
/SAW_TRIANG_A/V_TRIANGLE: C90.2, R170.2, TP25.1, U14.1; also elsewhere on the board
GND: C5.2, C6.2, C7.2, C8.2, R166.2, RV21.3; also elsewhere on the board
unnamed: C89.2, R165.1
unnamed: D32.1 (K), D33.1 (K), R165.2, R166.1, R167.1
unnamed: R168.1, RV21.2
unnamed: R169.2, R170.1
unnamed: R168.2, U14.3 (+)
unnamed: C90.1, R167.2, R169.1, U14.2 (-)

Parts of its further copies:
C1, C4: 100nF; C_0402_1005Metric; Manufacturer PartNumer GRM155R71E104KE14J
C2, C3: 1uF; C_0805_2012Metric; Manufacturer PartNumer GRM219R71E105MA88J
C64: 1nF; C_0402_1005Metric; Manufacturer PartNumer GRM155R71E103KA01J
C65: 100pF; C_0402_1005Metric; Manufacturer PartNumer GCM1555C1H101FA16J
D14, D15: 1N4148WT; D_SOD-523; Manufacturer PartNumer 1N4148WT
R95, R97, R99, R100: 10k; R_0402_1005Metric; Manufacturer PartNumer RT0402FRE0710KL
R96: 4.7k; R_0402_1005Metric; Manufacturer PartNumer RT0402FRE074K7L
R98: 1k; R_0402_1005Metric; Manufacturer PartNumer RT0402FRE071KL
RV8: 100k; Potentiometer_Bourns_3296W_Vertical; Manufacturer PartNumer 3296W-104-LF
TP15: V_TRIANGLE; TestPoint_Pad_1.0x1.0mm
U24: TL074; SOIC-14_3.9x8.7mm_P1.27mm; Manufacturer PartNumer TL074HIDR

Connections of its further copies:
+12V: C1.1, C3.1, RV8.1, U24.4 (V+); also elsewhere on the board
-12V: C2.1, C4.1, U24.11 (V-); also elsewhere on the board
/SAW_PULSE_A/V_PWM_CTRL: U24.9 (-); also elsewhere on the board
/SAW_PULSE_B/V_PULSE: U24.14; also elsewhere on the board
/SAW_PULSE_B/V_SAW: C64.1, D14.2 (A), U24.10 (+); also elsewhere on the board
/SAW_TRIANG_B/V_SAW_INVERTED: D15.2 (A); also elsewhere on the board
/SAW_TRIANG_B/V_TRIANGLE: C65.2, R100.2, TP15.1, U24.1; also elsewhere on the board
/TRIANG_SINE_B/V_SINE: U24.7; also elsewhere on the board
GND: C1.2, C2.2, C3.2, C4.2, R96.2, RV8.3, U24.12 (+); also elsewhere on the board
unnamed: C64.2, R95.1
unnamed: D14.1 (K), D15.1 (K), R95.2, R96.1, R97.1
unnamed 158: U24.5 (+); also elsewhere on the board
unnamed: R98.1, RV8.2
unnamed: R99.2, R100.1
unnamed 190: U24.8; also elsewhere on the board
unnamed: R98.2, U24.3 (+)
unnamed: C65.1, R97.2, R99.1, U24.2 (-)
unnamed 270: U24.6 (-); also elsewhere on the board
unnamed 271: U24.13 (-); also elsewhere on the board

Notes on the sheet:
Timmer: Set to 1.2V
SAW TO TRIANGLE WAVE
